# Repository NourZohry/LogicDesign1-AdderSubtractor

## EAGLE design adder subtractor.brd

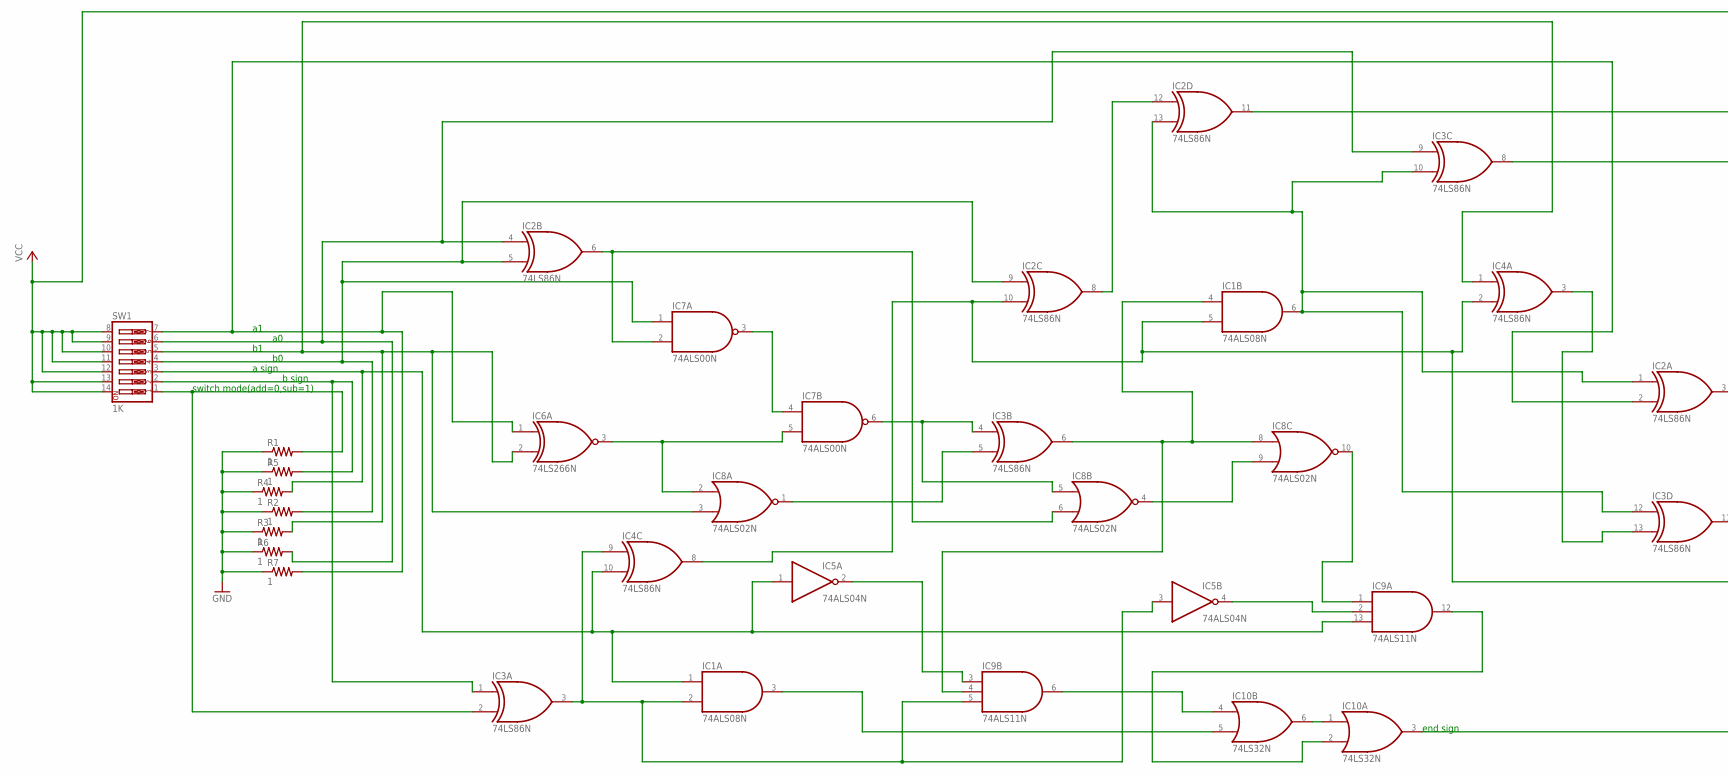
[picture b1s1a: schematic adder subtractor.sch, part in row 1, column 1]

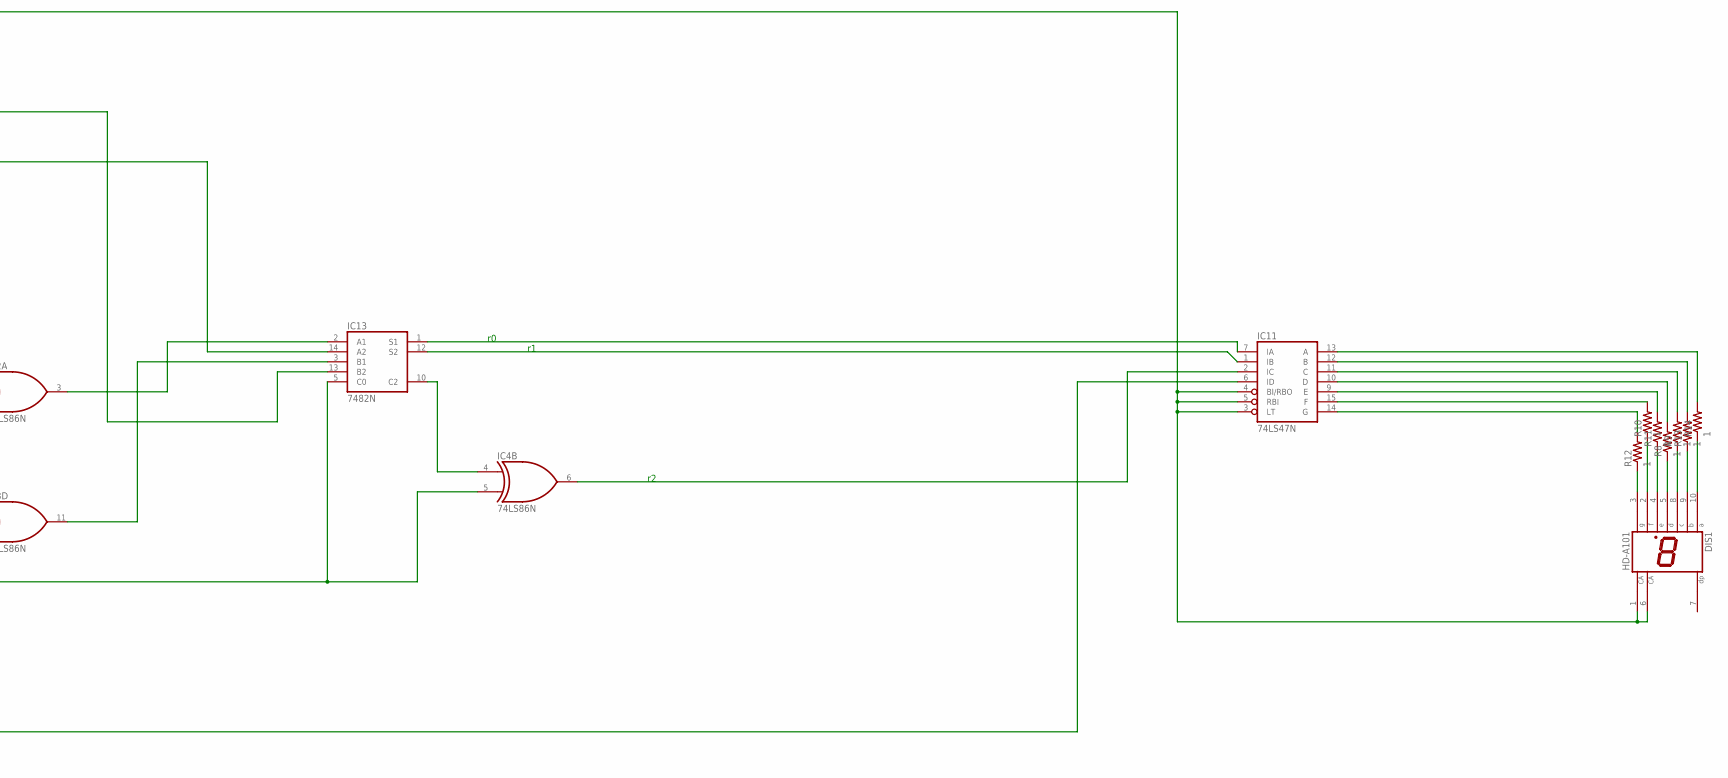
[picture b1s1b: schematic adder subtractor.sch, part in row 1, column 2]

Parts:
DIS1: HD-A101; HDSP-A
IC1: 74ALS08N; DIL14
IC2, IC3, IC4: 74LS86N; DIL14
IC5: 74ALS04N; DIL14
IC6: 74LS266N; DIL14
IC7: 74ALS00N; DIL14
IC8: 74ALS02N; DIL14
IC9: 74ALS11N; DIL14
IC10: 74LS32N; DIL14
IC11: 74LS47N; DIL16
IC13: 7482N; DIL14
R1, R2, R3, R4, R5, R6, R7, R8, R9, R10, R11, R12, R13, R14: 1; 0204V
SW1: 1K; EDG-07

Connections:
GND: IC1.7 (GND), IC2.7 (GND), IC3.7 (GND), IC4.7 (GND), IC5.7 (GND), IC6.7 (GND), IC7.7 (GND), IC8.7 (GND), IC9.7 (GND), IC10.7 (GND), IC11.8 (GND), IC13.7 (GND), R1.1, R2.1, R3.1, R4.1, R5.1, R6.1, R7.1
unnamed: IC2.2 (I1), IC6.1 (I0), R7.2, SW1.7
unnamed: IC2.4 (I0), IC3.9 (I0), R6.2, SW1.6
unnamed: IC4.1 (I0), IC6.2 (I1), IC8.3 (I1), R3.2, SW1.5
unnamed: IC2.5 (I1), IC2.9 (I0), IC7.1 (I0), R2.2, SW1.4
unnamed: IC1.1 (I0), IC4.10 (I1), IC5.1 (I), IC9.13 (I2), R4.2, SW1.3
unnamed: IC3.1 (I0), R5.2, SW1.2
unnamed: IC2.11 (O), IC13.13 (B2)
unnamed: IC2.6 (O), IC7.2 (I1), IC8.6 (I1)
unnamed: IC6.3 (O), IC7.5 (I1), IC8.2 (I0)
unnamed: IC7.3 (O), IC7.4 (I0)
unnamed: IC3.4 (I0), IC7.6 (O), IC8.5 (I0)
unnamed: IC3.5 (I1), IC8.1 (O)
unnamed: IC1.4 (I0), IC3.6 (O), IC8.8 (I0), IC9.4 (I1)
unnamed: IC8.4 (O), IC8.9 (I1)
unnamed: IC8.10 (O), IC9.1 (I0)
unnamed: IC1.2 (I1), IC3.3 (O), IC4.9 (I0), IC5.3 (I), IC9.5 (I2)
unnamed: IC5.4 (O), IC9.2 (I1)
unnamed: IC5.2 (O), IC9.3 (I0)
unnamed: IC9.6 (O), IC10.4 (I0)
unnamed: IC9.12 (O), IC10.2 (I1)
unnamed: IC1.3 (O), IC10.5 (I1)
unnamed: IC10.3 (O), IC11.6 (ID)
unnamed: IC1.5 (I1), IC2.10 (I1), IC4.2 (I1), IC4.5 (I1), IC4.8 (O), IC13.5 (C0)
unnamed: IC2.8 (O), IC2.12 (I0)
unnamed: IC1.6 (O), IC2.1 (I0), IC2.13 (I1), IC3.10 (I1), IC3.12 (I0)
unnamed: IC3.13 (I1), IC4.3 (O)
unnamed: IC2.3 (O), IC13.2 (A1)
unnamed: IC3.8 (O), IC13.14 (A2)
unnamed: IC3.11 (O), IC13.3 (B1)
unnamed: IC11.7 (IA), IC13.1 (S1)
unnamed: IC11.1 (IB), IC13.12 (S2)
unnamed: IC4.4 (I0), IC13.10 (C2)
unnamed: IC4.6 (O), IC11.2 (IC)
unnamed: DIS1.10 (A), R14.1
unnamed: DIS1.9 (B), R13.1
unnamed: DIS1.8 (C), R9.1
unnamed: DIS1.5 (D), R8.1
unnamed: DIS1.4 (E), R11.1
unnamed: DIS1.2 (F), R10.1
unnamed: DIS1.3 (G), R12.1
unnamed: IC11.13 (A), R14.2
unnamed: IC11.12 (B), R13.2
unnamed: IC11.11 (C), R9.2
unnamed: IC11.10 (D), R8.2
unnamed: IC11.9 (E), R11.2
unnamed: IC11.15 (F), R10.2
unnamed: IC11.14 (G), R12.2
unnamed: IC3.2 (I1), R1.2, SW1.1
unnamed: IC10.1 (I0), IC10.6 (O)
VCC: DIS1.1 (CA), DIS1.6 (CA), IC1.14 (VCC), IC2.14 (VCC), IC3.14 (VCC), IC4.14 (VCC), IC5.14 (VCC), IC6.14 (VCC), IC7.14 (VCC), IC8.14 (VCC), IC9.14 (VCC), IC10.14 (VCC), IC11.3 (LT), IC11.4 (BI/RBO), IC11.5 (RBI), IC11.16 (VCC), IC13.4 (VCC), SW1.8, SW1.9, SW1.10, SW1.11, SW1.12, SW1.13, SW1.14

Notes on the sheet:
a sign
b sign
switch mode(add=0,sub=1)
end sign

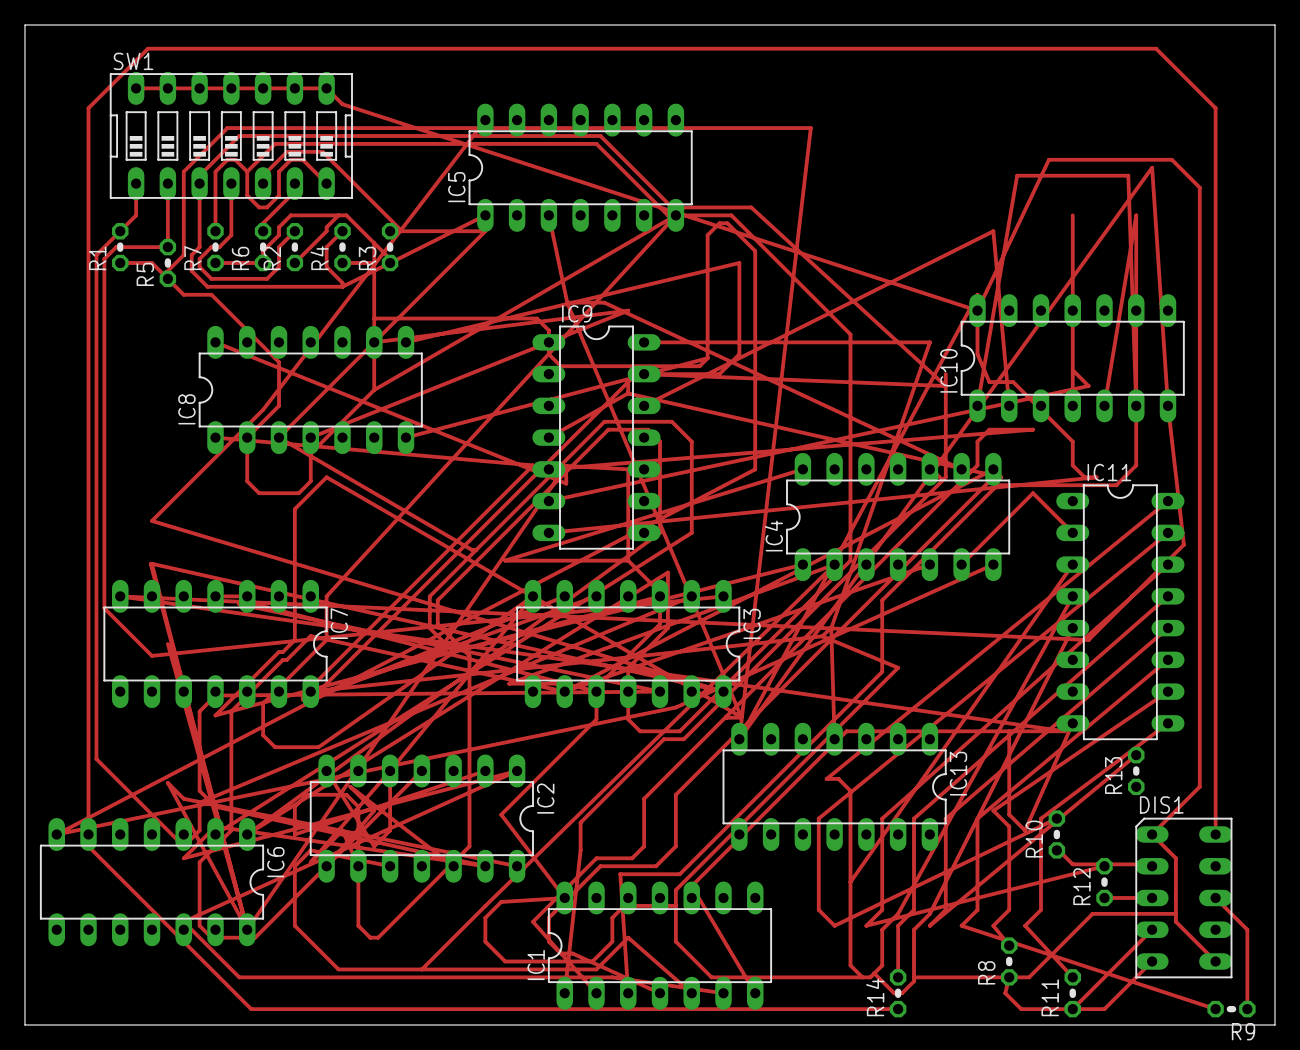
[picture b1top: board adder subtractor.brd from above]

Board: 2 copper layers, 100.0 x 80.0 mm, 28 parts (0 on the bottom side), 51 nets.
